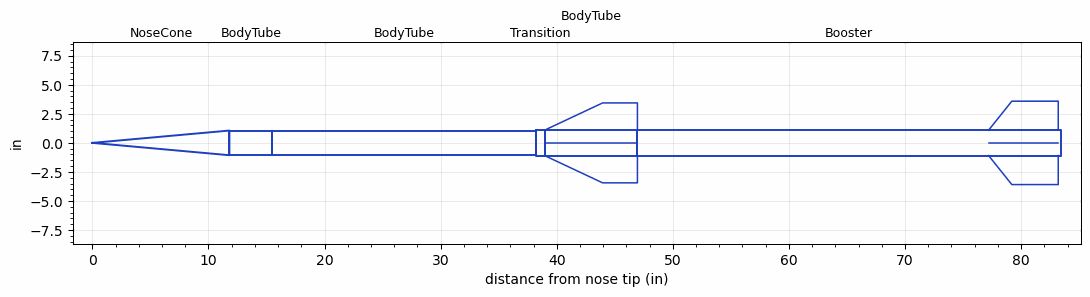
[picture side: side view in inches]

<RASAeroDocument>
 <FileVersion>2</FileVersion>
 <RocketDesign>
  <NoseCone>
   <Length>11.8</Length>
   <Diameter>2.125</Diameter>
   <Shape>Conical</Shape>
   <BluntRadius>0.0651</BluntRadius>
   <Location>0</Location>
  </NoseCone>
  <BodyTube>
   <Length>3.7</Length>
   <Diameter>2.125</Diameter>
   <Location>11.8</Location>
  </BodyTube>
  <BodyTube>
   <Length>22.7</Length>
   <Diameter>2.125</Diameter>
   <Location>15.5</Location>
  </BodyTube>
  <Transition>
   <Length>0.75</Length>
   <Diameter>2.185</Diameter>
   <Location>38.2</Location>
   <RearDiameter>2.185</RearDiameter>
  </Transition>
  <BodyTube>
   <Length>8</Length>
   <Diameter>2.185</Diameter>
   <Location>38.95</Location>
   <Fin>
    <Count>4</Count>
    <Chord>8</Chord>
    <Span>2.35</Span>
    <SweepDistance>5</SweepDistance>
    <TipChord>3</TipChord>
    <Thickness>0.08</Thickness>
    <LERadius>0.01</LERadius>
    <Location>8</Location>
    <AirfoilSection>Double Wedge</AirfoilSection>
    <FX1>1.5</FX1>
    <FX3>0.75</FX3>
   </Fin>
  </BodyTube>
  <Booster>
   <Length>36.5</Length>
   <Diameter>2.185</Diameter>
   <InsideDiameter>2.185</InsideDiameter>
   <RailGuideDiameter>0.4</RailGuideDiameter>
   <RailGuideHeight>0.4</RailGuideHeight>
   <Location>46.95</Location>
   <ShoulderLength>0</ShoulderLength>
   <Fin>
    <Count>4</Count>
    <Chord>6</Chord>
    <Span>2.5</Span>
    <SweepDistance>2</SweepDistance>
    <TipChord>4</TipChord>
    <Thickness>0.375</Thickness>
    <LERadius>0.02</LERadius>
    <Location>6.25</Location>
    <AirfoilSection>Double Wedge</AirfoilSection>
    <FX1>1.5</FX1>
   </Fin>
  </Booster>
  <Surface>Rough Camouflage Paint</Surface>
  <ModifiedBarrowman>True</ModifiedBarrowman>
  <Turbulence>True</Turbulence>
  <UseBooster1>False</UseBooster1>
  <UseBooster2>False</UseBooster2>
 </RocketDesign>
 <LaunchSite>
  <Altitude>4000</Altitude>
  <Pressure>29.92</Pressure>
  <RodAngle>2</RodAngle>
  <RodLength>10</RodLength>
  <Temperature>75</Temperature>
  <WindSpeed>7</WindSpeed>
 </LaunchSite>
 <Recovery>
  <Altitude1>0</Altitude1>
  <Altitude2>3000</Altitude2>
  <DeviceType1>Parachute</DeviceType1>
  <DeviceType2>Parachute</DeviceType2>
  <Event1>False</Event1>
  <Event2>False</Event2>
  <Size1>4</Size1>
  <Size2>28</Size2>
  <EventType1>Apogee</EventType1>
  <EventType2>Altitude</EventType2>
  <CD1>1</CD1>
  <CD2>1.75</CD2>
 </Recovery>
 <SimulationList>
  <Simulation>
   <SustainerEngine>L1081  (boostkareilley)</SustainerEngine>
   <SustainerLaunchWt>7.3</SustainerLaunchWt>
   <SustainerNozzleDiameter>1.905</SustainerNozzleDiameter>
   <SustainerCG>27.8</SustainerCG>
   <SustainerIgnitionDelay>8</SustainerIgnitionDelay>
   <Booster1Engine>L1426BooskaFastNC  (Polaris)</Booster1Engine>
   <Booster1LaunchWt>14.3</Booster1LaunchWt>
   <Booster1SeparationDelay>0.02</Booster1SeparationDelay>
   <Booster1IgnitionDelay>0</Booster1IgnitionDelay>
   <Booster1CG>45.7</Booster1CG>
   <Booster1NozzleDiameter>1.9</Booster1NozzleDiameter>
   <IncludeBooster1>True</IncludeBooster1>
   <Booster2Delay>0</Booster2Delay>
   <IncludeBooster2>False</IncludeBooster2>
   <TimetoApogee>71.21628</TimetoApogee>
   <MaxAltitude>87978.45</MaxAltitude>
   <MaxVelocity>4641.511</MaxVelocity>
   <OptimumWt>9.862499</OptimumWt>
   <OptimumMaxAlt>9.862499</OptimumMaxAlt>
  </Simulation>
 </SimulationList>
</RASAeroDocument>
